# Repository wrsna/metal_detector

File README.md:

# metal_detector
This is project created for summer camp on our faculty for kids. Other members of our team made the board i just make some small changes and bring board to life

 Files are mostly created with Eagle software it is more or less schematic and board view and backup files

some of the files are gerber files for manufactoring.

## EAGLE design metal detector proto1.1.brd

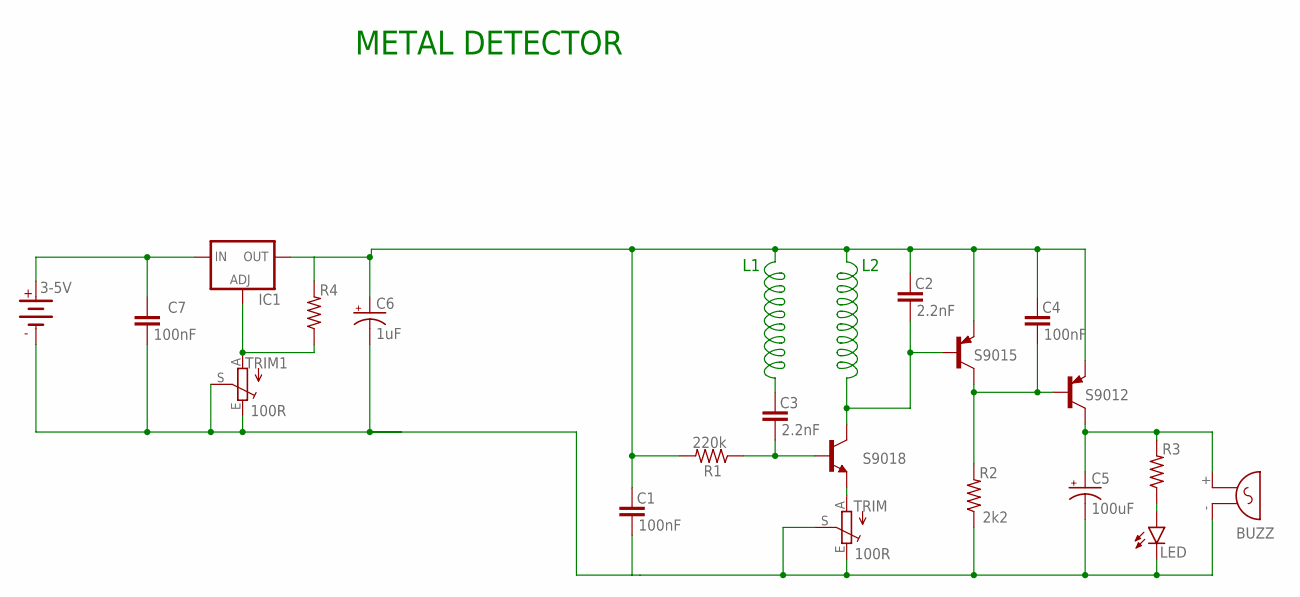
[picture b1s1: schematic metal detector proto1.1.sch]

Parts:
3-5V: 3-5V; AB9V
BUZZ: F/QMX
C1, C4, C7: 100nF; BOX_SMALL
C2, C3: 2.2nF; BOX_SMALL
C5: 100uF; 063_025
C6: 1uF; 063_025
IC1: LM138-TS; TO220S
LED: LED5MM
R1: 220k; R0207/3
R2: 2k2; R0207/3
R3, R4: R_.3B; R0207/3
S9012: S9012; TO92-EBC
S9015: S9015; TO92-EBC
S9018: S9018; TO92-EBC
TRIM, TRIM1: 100R; RJ9W

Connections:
GND: 3-5V.-, BUZZ.- (1), C1.2, C5.-, C6.-, C7.2, LED.K (C), R2.1, TRIM.E, TRIM.S, TRIM1.E, TRIM1.S
unnamed: 3-5V.+, C7.1, IC1.3 (IN)
unnamed: C4.2, R2.2, S9012.2 (B), S9015.3 (C)
unnamed: BUZZ.+ (2), C5.+, R3.2, S9012.3 (C)
unnamed: LED.A, R3.1
unnamed: C1.1, C2.1, C2.2, C3.1, C4.1, C6.+, IC1.2 (OUT), R1.2, R4.2, S9012.1 (E), S9015.1 (E), S9015.2 (B), S9018.3 (C)
unnamed: IC1.1 (ADJ), R4.1, TRIM1.A
unnamed: S9018.1 (E), TRIM.A
unnamed: C3.2, R1.1, S9018.2 (B)

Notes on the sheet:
METAL DETECTOR

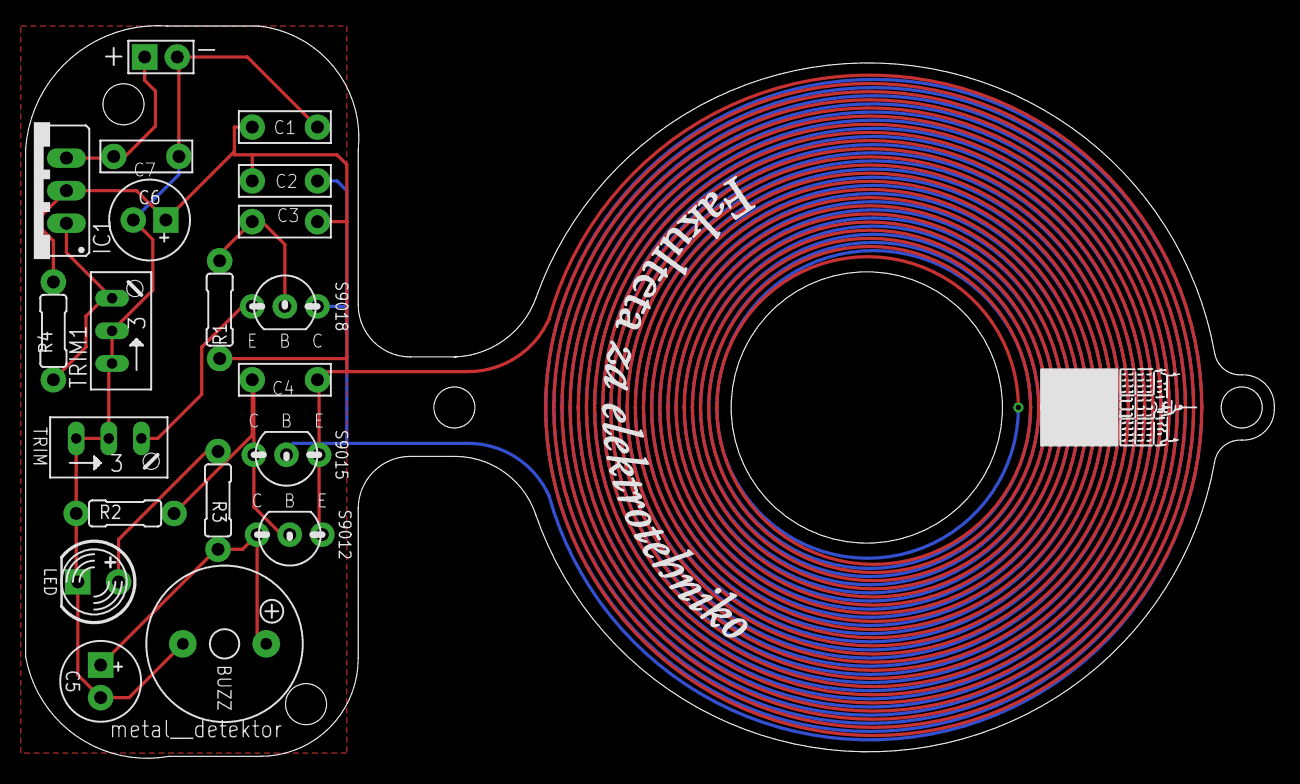
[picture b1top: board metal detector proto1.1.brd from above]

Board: 2 copper layers, 97.3 x 57.1 mm, 20 parts (0 on the bottom side), 9 nets.

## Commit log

2020-10-03 Add files via upload
    schematics and pictures of the detector
